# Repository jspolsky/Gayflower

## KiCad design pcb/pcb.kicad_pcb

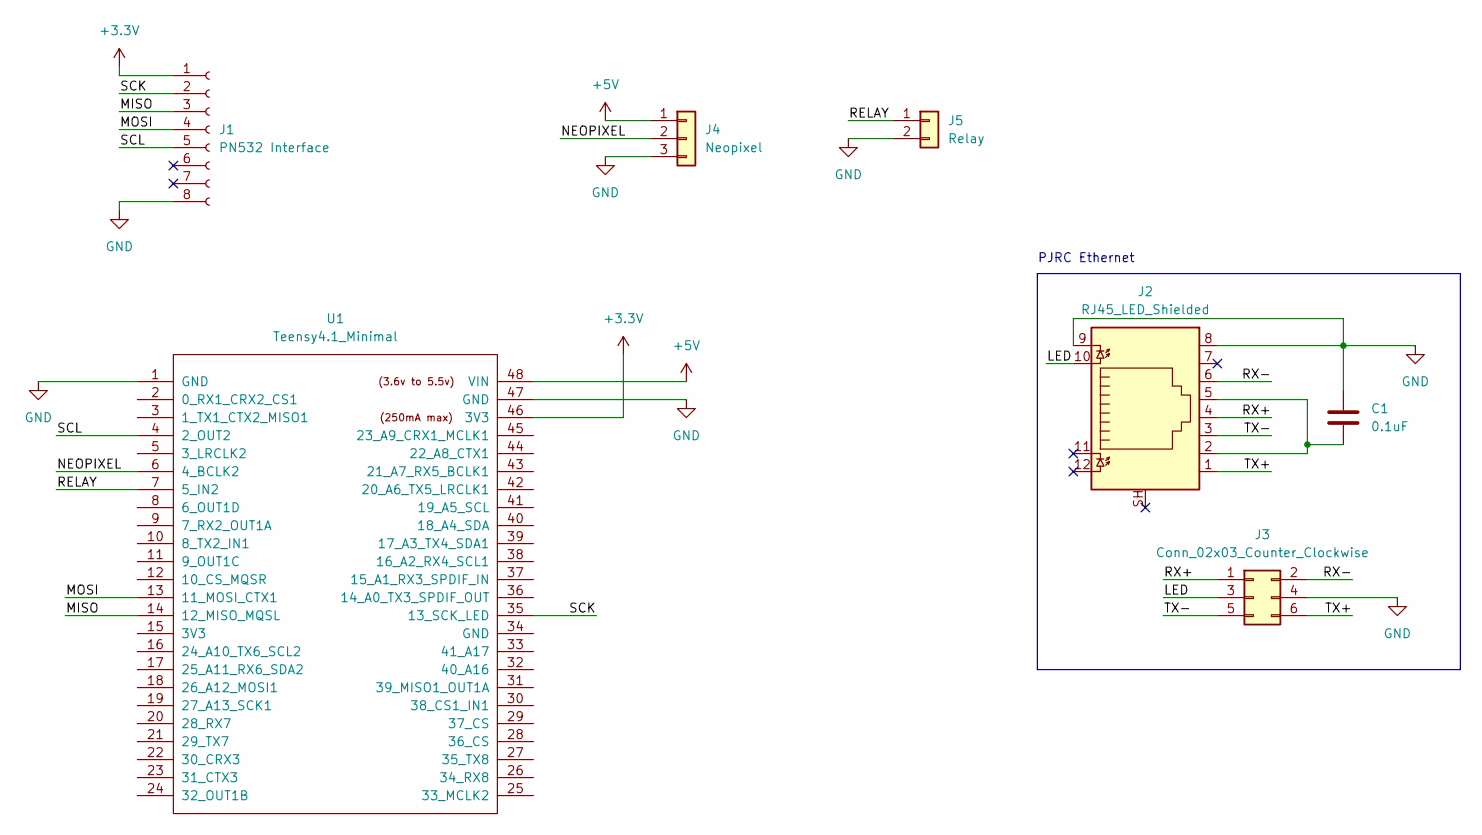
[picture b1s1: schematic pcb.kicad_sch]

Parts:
C1: 0.1uF; C_0805_2012Metric_Pad1.18x1.45mm_HandSolder
J1: PN532 Interface; PinHeader_1x08_P2.54mm_Vertical
J2: RJ45_LED_Shielded; RJ45_Cetus_J1B1211CCD_Horizontal
J3: Conn_02x03_Counter_Clockwise; PinHeader_2x03_P2.00mm_Vertical
J4: Neopixel; TerminalBlock_bornier-3_P5.08mm
J5: Relay; TerminalBlock_bornier-2_P5.08mm
U1: Teensy4.1_Minimal; Teensy41_Minimal

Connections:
+3.3V: J1.1, U1.46 (3V3)
+5V: J4.1, U1.48 (VIN)
/LED: J2.10, J3.3
/MISO: J1.3, U1.14 (12_MISO_MQSL)
/MOSI: J1.4, U1.13 (11_MOSI_CTX1)
/NEOPIXEL: J4.2, U1.6 (4_BCLK2)
/RELAY: J5.1, U1.7 (5_IN2)
/RX+: J2.4, J3.1
/RX-: J2.6, J3.2
/SCK: J1.2, U1.35 (13_SCK_LED)
/SCL: J1.5, U1.4 (2_OUT2)
/TX+: J2.1, J3.6
/TX-: J2.3, J3.5
GND: C1.1, J1.8, J2.8, J2.9, J3.4, J4.3, J5.2, U1.1 (GND), U1.47 (GND)
unnamed: C1.2, J2.2, J2.5

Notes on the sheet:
PJRC Ethernet

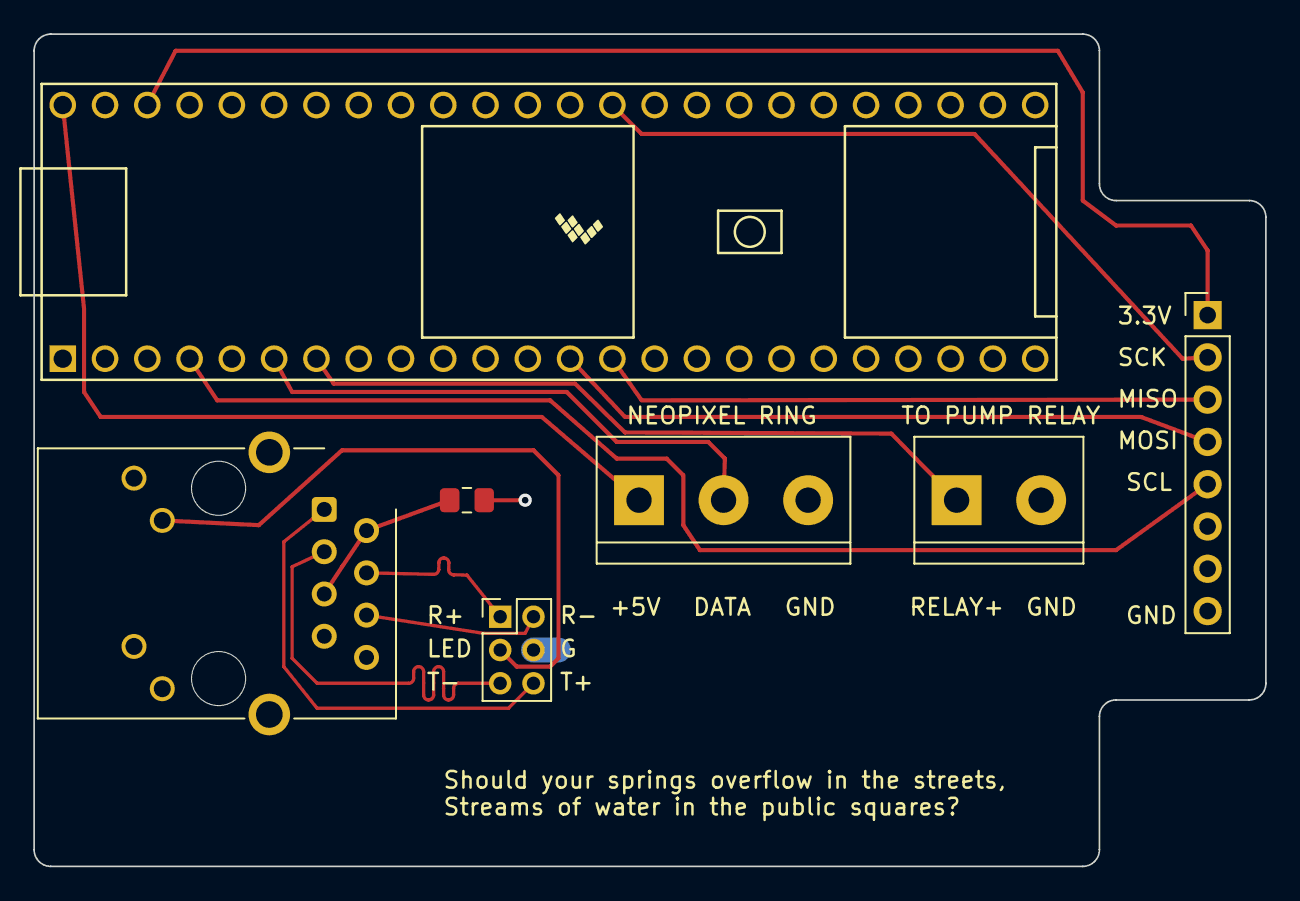
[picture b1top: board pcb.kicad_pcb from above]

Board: 2 copper layers, 74.0 x 50.0 mm, 7 parts (0 on the bottom side), 15 nets.

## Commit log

2024-03-21 green dot indicator while initializing
2024-03-22 simple test of relay control - it works!
2024-03-22 turtle logo for enclosure
2024-03-22 helper PCB for teensy, ethernet, PN532 breakout
2024-03-26 fusion 360 model of key fob
2024-04-06 3d prints
2024-04-06 3d prints - case of activation controller
2024-04-06 skeleton server - just enough to show the protocol
2024-04-06 a little refactoring
2024-04-06 removed a little random debugging
2024-04-07 Added important error handling to tcp server
2024-04-08 More implementation
2024-04-08 just a little debugging message
2024-04-08 send swipe messages
2024-04-08 work on reading responses
2024-04-09 pass back pump time
2024-04-09 ok i actually think the clients all work perfectly now
2024-04-14 ubuntu configuration
2024-04-14 hardcoded IP for server
2024-04-14 initialize nextjs server oogway
2024-04-16 init page layout and font
2024-04-16 try to restart ethernet if connection didn't work
2024-04-20 setup pages and sqlite tables
2024-04-20 ability to add/edit/delete turtles from the website
2024-04-20 refresh db schema and update readme
2024-04-20 exclude scripts from bundle
2024-04-20 setup tcp server, config pages, ability to read/edit/delete configs from UI, tcp server on 3001 reads pump time in seconds
2024-04-20 bugfix
2024-04-20 cleanup
2024-04-21 split tcp and http servers into separate process
2024-04-28 refactor + changes
2024-04-28 DB cleanup
2024-04-28 log messages
2024-04-28 turtle page updated + cleanup
2024-04-28 bug fix
2024-04-29 listen to port 80
2024-04-29 show unassigned in home page, add swipe stats
2024-04-30 renamed notes file
2024-05-15 lint + prettier added
2024-05-15 prettier + formatting
2024-05-25 Update unassigned page
2024-05-25 watermaster
2024-05-26 add package and update readme
2024-05-27 Updated info on configuring Wifi Adapter
